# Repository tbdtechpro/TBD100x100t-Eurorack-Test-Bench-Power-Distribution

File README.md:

# TBD100x100t Eurorack Test Bench Power Distribution
 Eurorack distribution board with banana jack sockets for inputs and test probe sockets and a terminal block at the end of the circuit.

 This is part of a series of 100mm x 100mm Power Distribution boards I'm putting together. There is also a default board and an extension board.
 The size was chosen to allow for cheap manufacture with the prototype PCB providers.

 TBD-100x100t is intended for test bench usage: checking DIY modules and power supplies before they go anywhere near a rack. I run mine from a Mean Well triple output supply (+12v, -12v and 5v) in an enclosure with banana jacks.

## Rev 0.2 - now in KiCad
 The board was originally drawn in DipTrace back in 2020. It has now been migrated to KiCad 9 and reworked to fix some issues with that original draft.
 I have not had rev 0.2 manufactured yet, so it is untested at this time. It passes KiCad's ERC and DRC checks.

 What changed from the original draft:
 - The 5v rail is finished. On the original the 5v bus was never joined to its filter, two of its capacitors were not grounded and 5v never reached the terminal block.
 - Four 16 pin headers instead of six. The original headers were too close together to use without skipping every other one, at least with the cables I had. They are now 22mm apart.
 - The banana jacks are on the standard 19.05mm spacing with 1.6mm holes. The original spacing and holes were too small for the Cal Test jacks in the BOM.
 - Each rail is still a Pi filter but with a 10uH inductor in place of the ferrite bead (which is now obsolete), and most of the capacitance moved to the bus side: 47uF, 10uH, then 1000uF with 10uF and 100nF ceramics.
 - Each rail has a resettable fuse, a Schottky diode to ground so a swapped lead trips the fuse, and an LED after the fuse.
 - Each rail has a two pin link. Pull the jumper and put a multimeter across the pins to read how much current a module draws.
 - Loop test points at each input show what the supply is delivering. The four test probe sockets are on the bus and show what the modules see. They now sit at the top edge of the board so a multimeter probe can reach them. There are two ground loops for an oscilloscope clip.

 The headers have pin 1 (-12v, the red stripe) at the bottom, same as the original.

## Files
 - `kicad/` is the KiCad 9 project: schematic and board.
 - `TBD100x100t_rev0.2_schematic.pdf` is the schematic.
 - `TBD100x100t_rev0.2_gerbers.zip` has the gerbers and drill files.
 - `TBD 100x100t  BOM.csv` has the parts and values with manufacturer part numbers.
 - `3drender.png` and `3drender-top.png` are renders of the board.
 - `original-diptrace/` keeps the 2020 DipTrace files, gerbers, BOM and render, plus `kicad-port/`, a KiCad copy of that original board exactly as it was drawn, faults included.

 The banana jack, test probe socket, fuse, terminal block and inductor footprints come from my [tbd-kicad](https://github.com/tbdtechpro/tbd-kicad) library. The board file carries its own copies so it opens without the library, but you will want it if you plan to edit those parts.

## Things to check before ordering
 - The test probe socket footprint follows the pattern from the 2020 board. Cinch only supplies the drawing on request, so I have not been able to verify it.
 - The header spacing is close to, but not exactly, the spacing I know works with my cables.
 - The -12v fuse is 1.1A like the other two, which is more than the 0.5A a Mean Well RT-65B is rated for on that rail.

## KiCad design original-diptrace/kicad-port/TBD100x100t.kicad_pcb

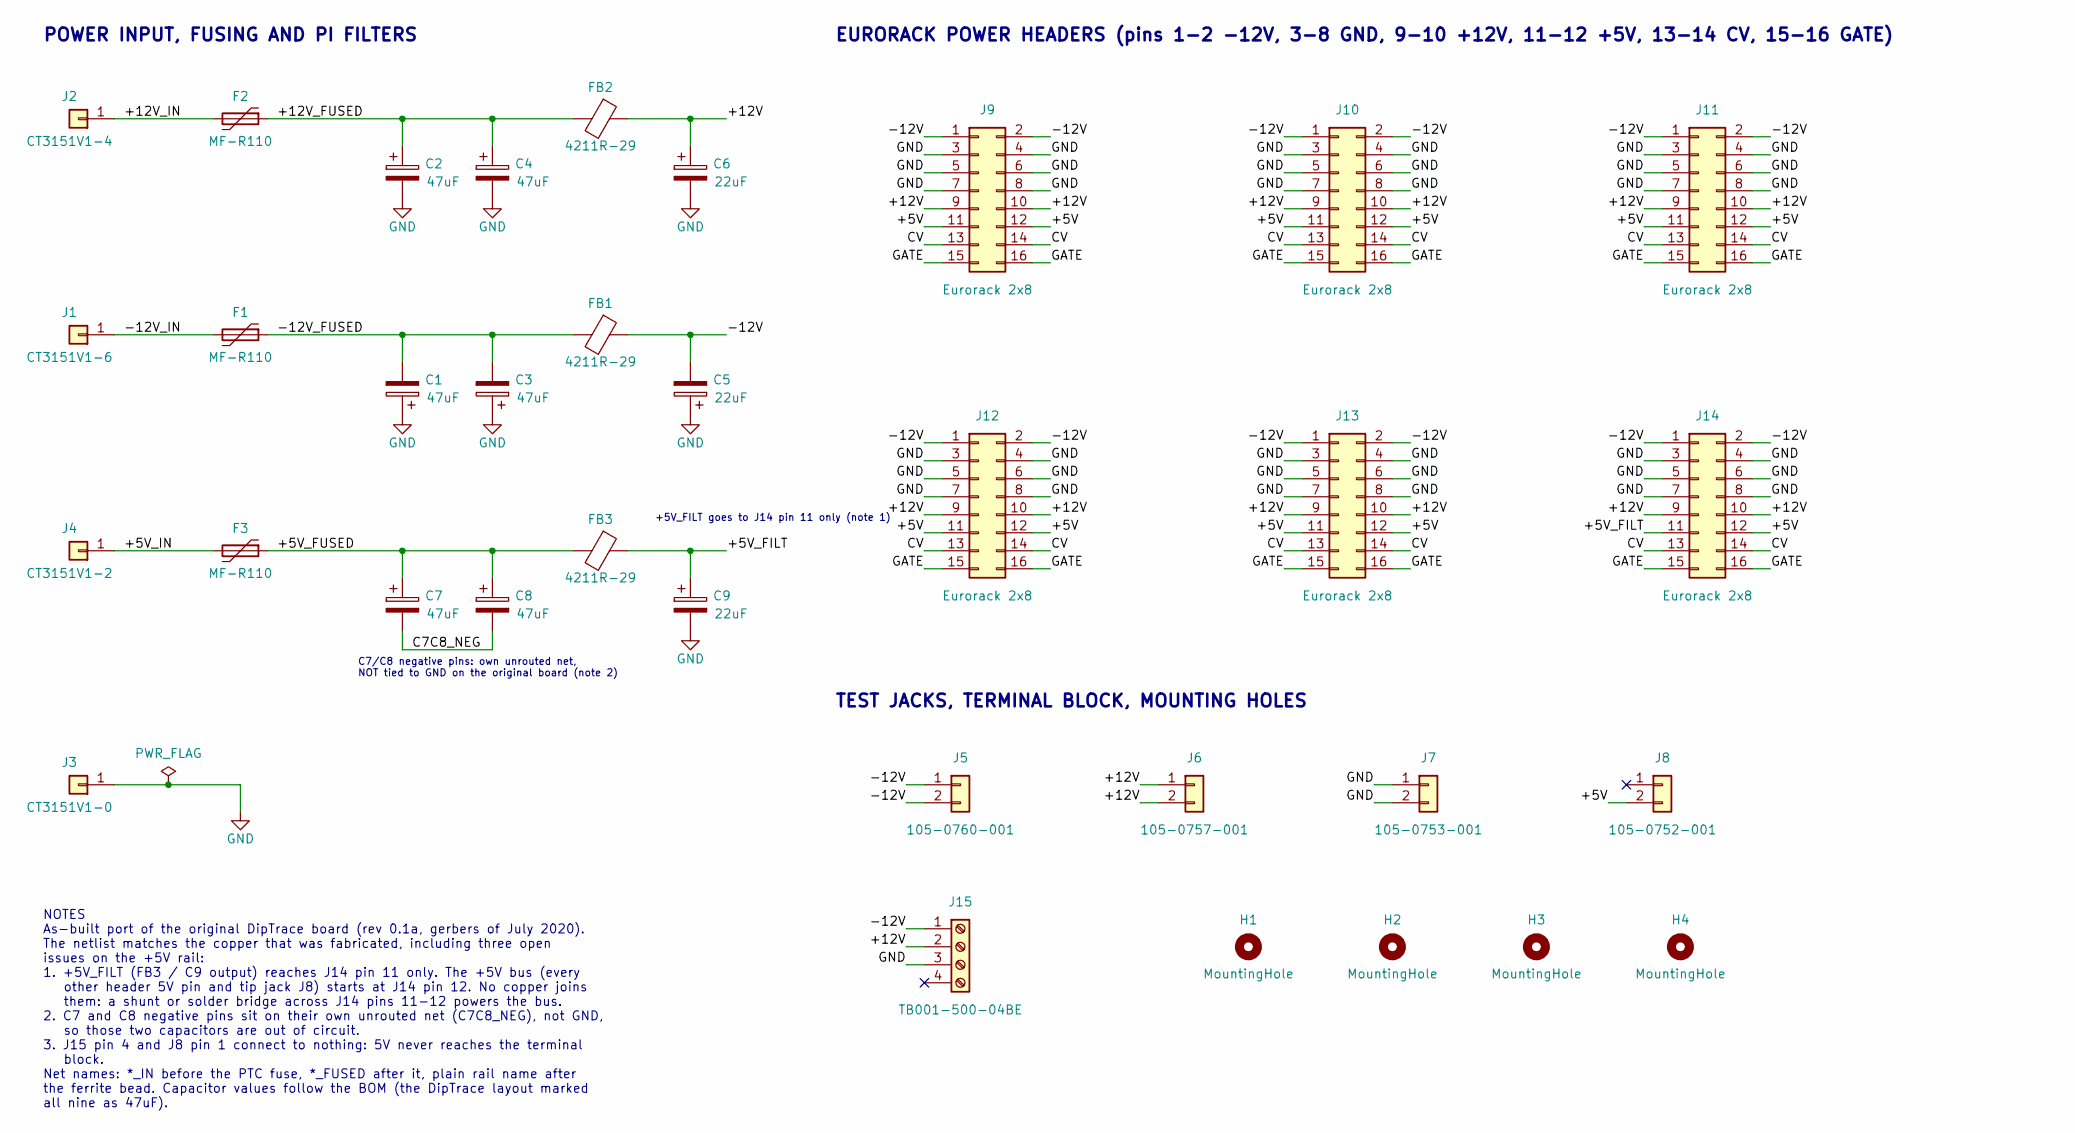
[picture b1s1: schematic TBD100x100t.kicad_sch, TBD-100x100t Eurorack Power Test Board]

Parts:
C1, C2, C3, C4, C7, C8: 47uF; CP_Radial_D4.4mm_P5.08mm; Mouser 667-EEU-FC1J470B
C5, C6, C9: 22uF; CP_Radial_D4.4mm_P5.08mm; Mouser 667-EEU-FC1H220B
F1, F2, F3: MF-R110; Fuse_PTC_Bourns_MF-R110_P5.1mm; Mouser 652-MF-R110-2
FB1, FB2, FB3: 4211R-29; FerriteBead_Axial_L13.8mm_D3.5mm_P27.8mm; Mouser 807-4211R-29TR
H1, H2, H3, H4: MountingHole; MountingHole_3.0mm_NPTH
J1: CT3151V1-6; BananaJack_CalTest_CT3151V1_Vertical; Mouser 510-CT3151V1-6
J2: CT3151V1-4; BananaJack_CalTest_CT3151V1_Vertical; Mouser 510-CT3151V1-4
J3: CT3151V1-0; BananaJack_CalTest_CT3151V1_Vertical; Mouser 510-CT3151V1-0
J4: CT3151V1-2; BananaJack_CalTest_CT3151V1_Vertical; Mouser 510-CT3151V1-2
J5: 105-0760-001; TipJack_Johnson_105-07xx_Horizontal; Mouser 530-105-0760-1
J6: 105-0757-001; TipJack_Johnson_105-07xx_Horizontal; Mouser 530-105-0757-1
J7: 105-0753-001; TipJack_Johnson_105-07xx_Horizontal; Mouser 530-105-0753-150
J8: 105-0752-001; TipJack_Johnson_105-07xx_Horizontal; Mouser 530-105-0752-1
J9, J10, J11, J12, J13, J14: Eurorack 2x8; PinHeader_2x08_P2.54mm_Eurorack; Mouser 517-N2516-6002RB
J15: TB001-500-04BE; TerminalBlock_CUI_TB001-500-04BE_1x04_P5.00mm; Mouser 490-TB001-500-04BE

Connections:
/+5V: J8.2, J9.11, J9.12, J10.11, J10.12, J11.11, J11.12, J12.11, J12.12, J13.11, J13.12, J14.12
/+5V_FILT: C9.1, FB3.1, J14.11
/+5V_FUSED: C7.1, C8.1, F3.1, FB3.2
/+5V_IN: F3.2, J4.1
/+12V: C6.1, FB2.1, J6.1, J6.2, J9.9, J9.10, J10.9, J10.10, J11.9, J11.10, J12.9, J12.10, J13.9, J13.10, J14.9, J14.10, J15.2
/+12V_FUSED: C2.1, C4.1, F2.1, FB2.2
/+12V_IN: F2.2, J2.1
/-12V: C5.2, FB1.1, J5.1, J5.2, J9.1, J9.2, J10.1, J10.2, J11.1, J11.2, J12.1, J12.2, J13.1, J13.2, J14.1, J14.2, J15.1
/-12V_FUSED: C1.2, C3.2, F1.1, FB1.2
/-12V_IN: F1.2, J1.1
/C7C8_NEG: C7.2, C8.2
/CV: J9.13, J9.14, J10.13, J10.14, J11.13, J11.14, J12.13, J12.14, J13.13, J13.14, J14.13, J14.14
/GATE: J9.15, J9.16, J10.15, J10.16, J11.15, J11.16, J12.15, J12.16, J13.15, J13.16, J14.15, J14.16
GND: C1.1, C2.2, C3.1, C4.2, C5.1, C6.2, C9.2, J3.1, J7.1, J7.2, J9.3, J9.4, J9.5, J9.6, J9.7, J9.8, J10.3, J10.4, J10.5, J10.6, J10.7, J10.8, J11.3, J11.4, J11.5, J11.6, J11.7, J11.8, J12.3, J12.4, J12.5, J12.6, J12.7, J12.8, J13.3, J13.4, J13.5, J13.6, J13.7, J13.8, J14.3, J14.4, J14.5, J14.6, J14.7, J14.8, J15.3

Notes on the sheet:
POWER INPUT, FUSING AND PI FILTERS
C7/C8 negative pins: own unrouted net, NOT tied to GND on the original board (note 2)
+5V_FILT goes to J14 pin 11 only (note 1)
EURORACK POWER HEADERS (pins 1-2 -12V, 3-8 GND, 9-10 +12V, 11-12 +5V, 13-14 CV, 15-16 GATE)
TEST JACKS, TERMINAL BLOCK, MOUNTING HOLES
NOTES As-built port of the original DipTrace board (rev 0.1a, gerbers of July 2020). The netlist matches the copper that was fabricated, including three open issues on the +5V rail: 1. +5V_FILT (FB3 / C9 output) reaches J14 pin 11 only. The +5V bus (every other header 5V pin and tip jack J8) starts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

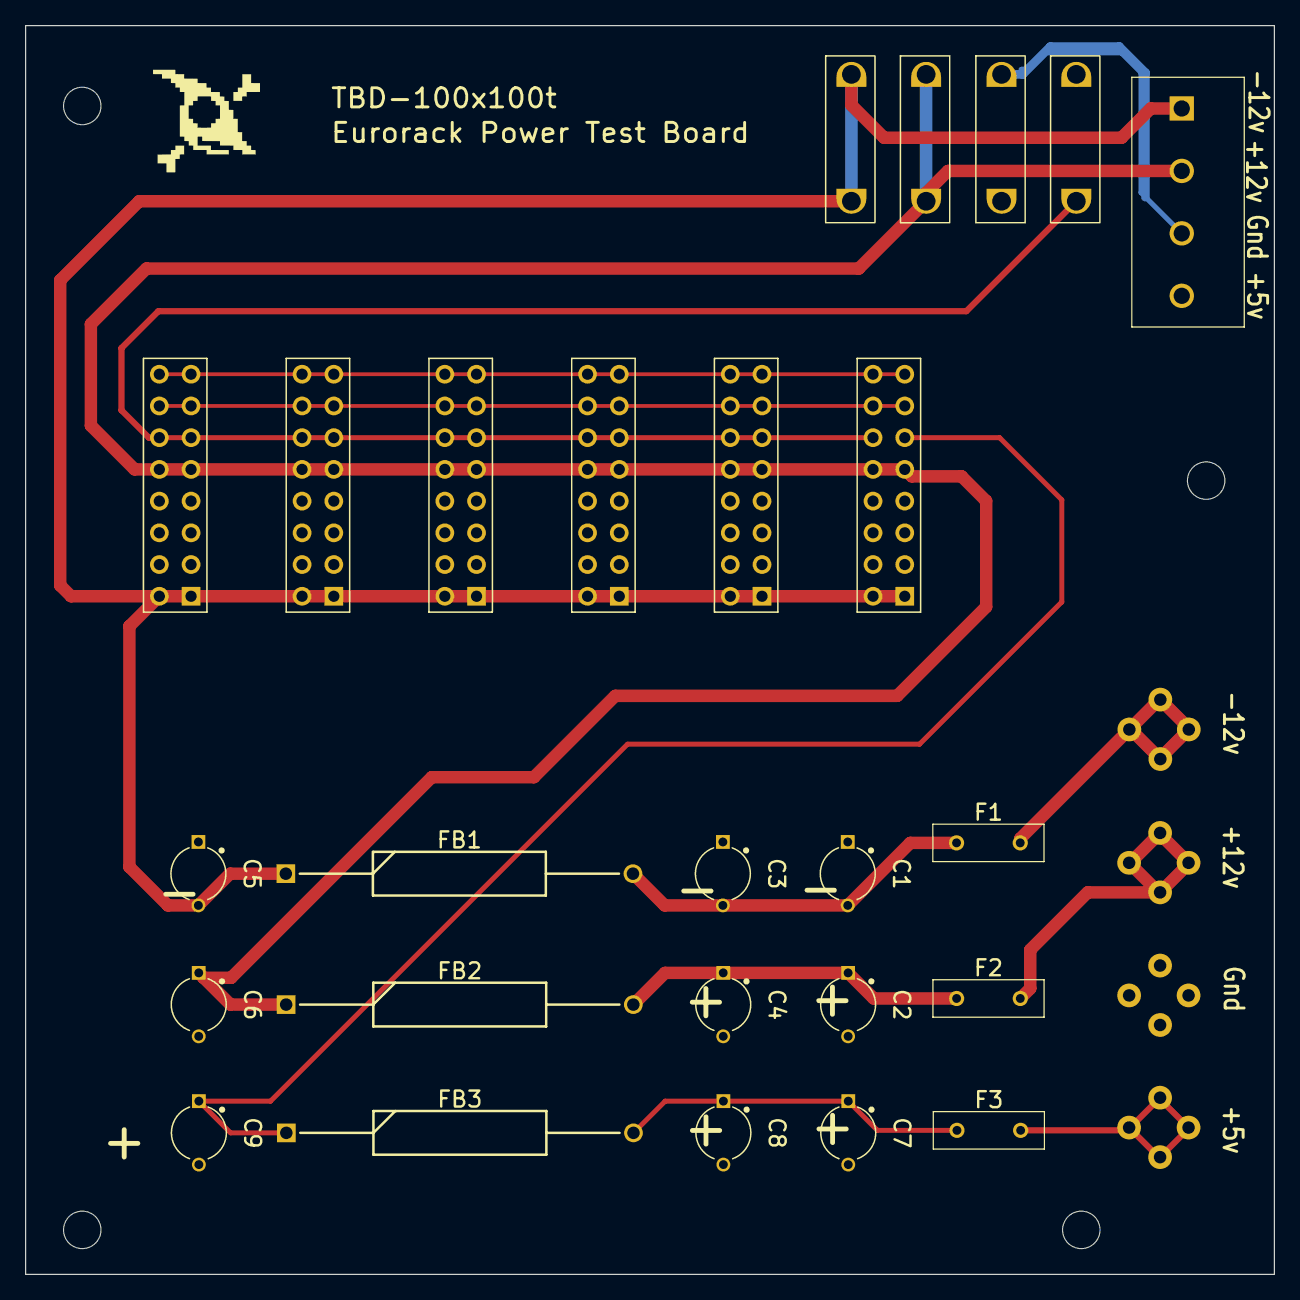
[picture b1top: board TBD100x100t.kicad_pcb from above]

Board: 2 copper layers, 100.0 x 100.0 mm, 34 parts (0 on the bottom side), 14 nets.

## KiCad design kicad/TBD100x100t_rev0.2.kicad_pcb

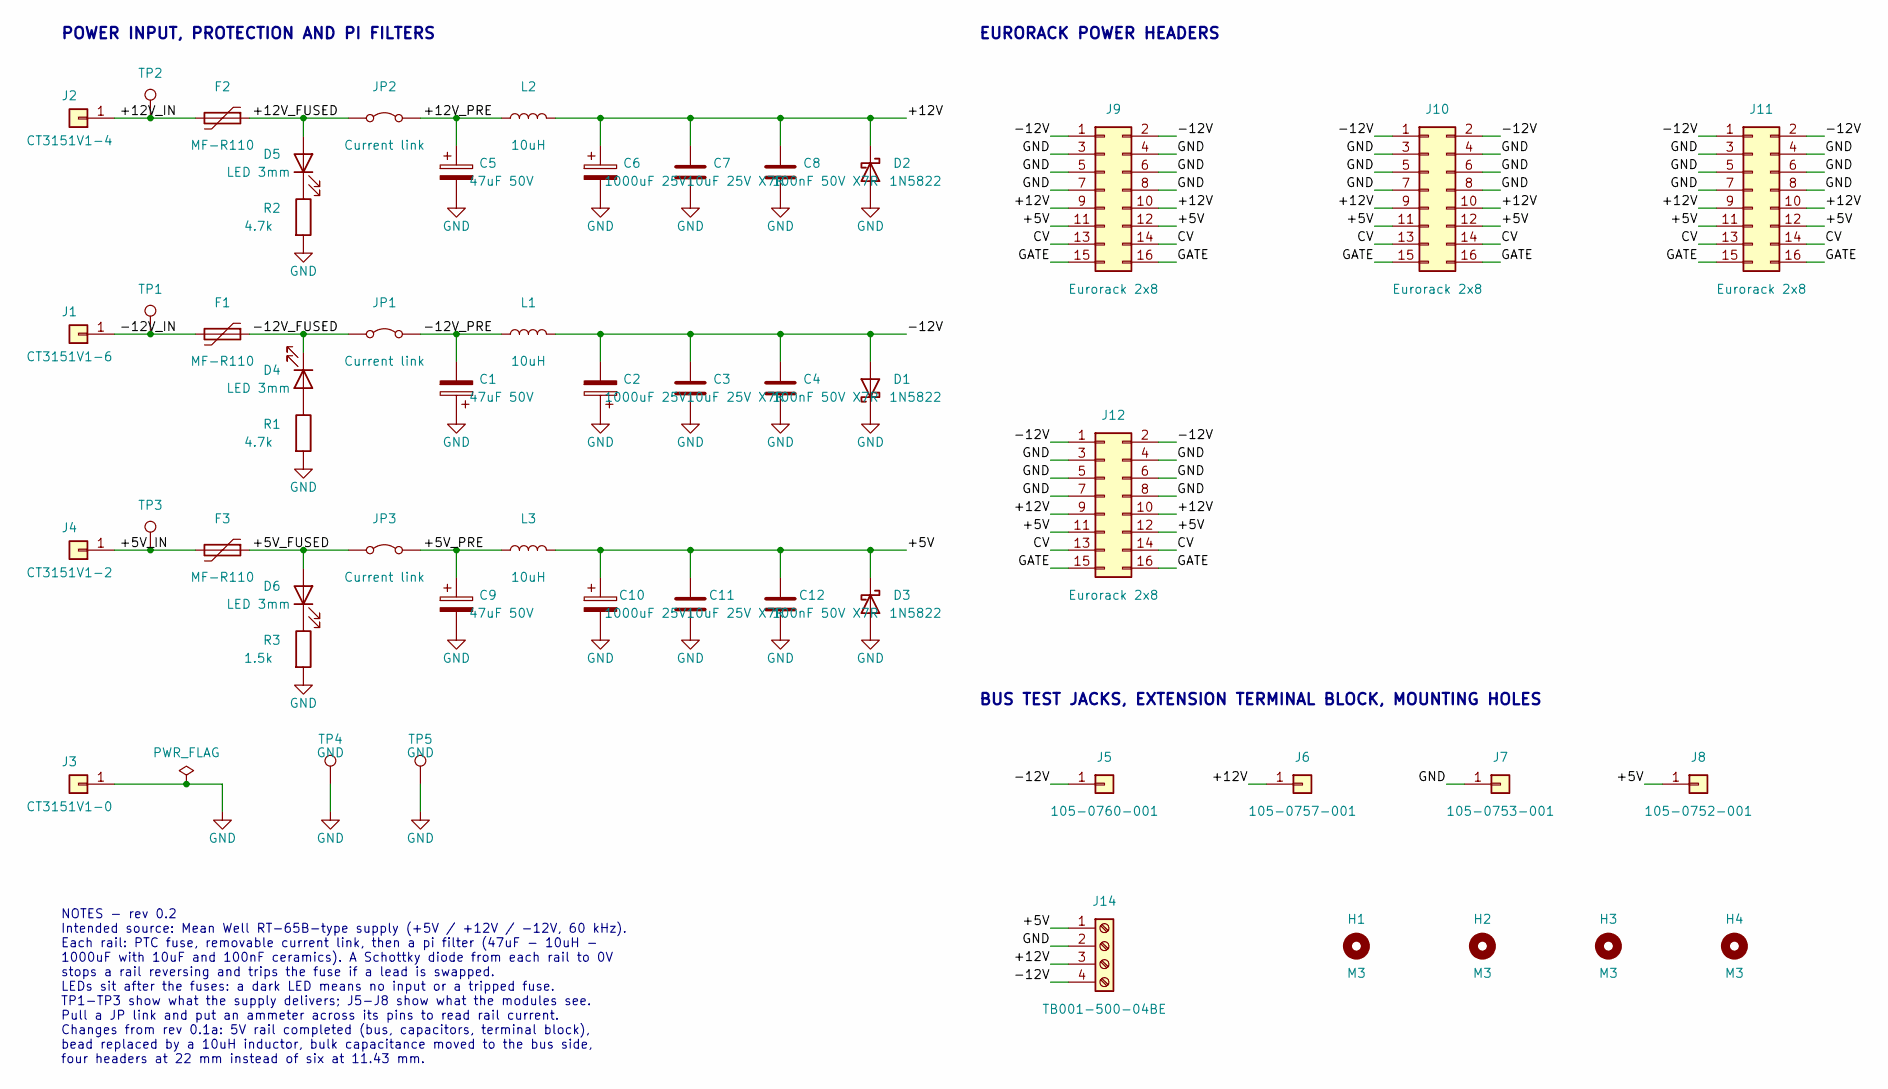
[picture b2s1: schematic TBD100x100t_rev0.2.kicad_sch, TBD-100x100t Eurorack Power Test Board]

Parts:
C1, C5, C9: 47uF 50V; CP_Radial_D6.3mm_P2.50mm; MPN EEU-FR1H470
C2, C6, C10: 1000uF 25V; CP_Radial_D10.0mm_P5.00mm; MPN EEU-FR1E102
C3, C7, C11: 10uF 25V X7R; C_Disc_D6.0mm_W4.4mm_P5.00mm; MPN FG26X7R1E106KRT06
C4, C8, C12: 100nF 50V X7R; C_Disc_D5.0mm_W2.5mm_P5.00mm; MPN FG28X7R1H104KNT06
D1, D2, D3: 1N5822; D_DO-201AD_P12.70mm_Horizontal; MPN 1N5822
D4, D5, D6: LED 3mm; LED_D3.0mm
F1, F2, F3: MF-R110; Fuse_Bourns_MF-R110; MPN MF-R110
H1, H2, H3, H4: M3; MountingHole_3.2mm_M3
J1: CT3151V1-6; Banana_CalTest_CT3151V1_Vertical; MPN CT3151V1-6
J2: CT3151V1-4; Banana_CalTest_CT3151V1_Vertical; MPN CT3151V1-4
J3: CT3151V1-0; Banana_CalTest_CT3151V1_Vertical; MPN CT3151V1-0
J4: CT3151V1-2; Banana_CalTest_CT3151V1_Vertical; MPN CT3151V1-2
J5: 105-0760-001; TipJack_Johnson_105-075x_Horizontal_P10.16mm; MPN 105-0760-001
J6: 105-0757-001; TipJack_Johnson_105-075x_Horizontal_P10.16mm; MPN 105-0757-001
J7: 105-0753-001; TipJack_Johnson_105-075x_Horizontal_P10.16mm; MPN 105-0753-001
J8: 105-0752-001; TipJack_Johnson_105-075x_Horizontal_P10.16mm; MPN 105-0752-001
J9, J10, J11, J12: Eurorack 2x8; IDC-Header_2x08_P2.54mm_Vertical; MPN N2516-6002RB
J14: TB001-500-04BE; TerminalBlock_SameSky_TB001-500-04_1x04_P5.00mm; MPN TB001-500-04BE
JP1, JP2, JP3: Current link; PinHeader_1x02_P2.54mm_Vertical
L1, L2, L3: 10uH; L_Radial_D8.7mm_H12.0mm_P5.00mm_Bourns_RLB0914; MPN RLB0914-100KL
R1, R2: 4.7k; R_Axial_DIN0207_L6.3mm_D2.5mm_P7.62mm_Horizontal
R3: 1.5k; R_Axial_DIN0207_L6.3mm_D2.5mm_P7.62mm_Horizontal
TP1: -12V IN; TestPoint_Keystone_5010-5014_Multipurpose; MPN 5010
TP2: +12V IN; TestPoint_Keystone_5010-5014_Multipurpose; MPN 5010
TP3: +5V IN; TestPoint_Keystone_5010-5014_Multipurpose; MPN 5010
TP4, TP5: GND; TestPoint_Keystone_5010-5014_Multipurpose; MPN 5011

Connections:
/+5V: C10.1, C11.1, C12.1, D3.1 (K), J8.1, J9.11, J9.12, J10.11, J10.12, J11.11, J11.12, J12.11, J12.12, J14.1, L3.2
/+5V_FUSED: D6.2 (A), F3.1, JP3.1 (A)
/+5V_IN: F3.2, J4.1, TP3.1
/+5V_PRE: C9.1, JP3.2 (B), L3.1
/+12V: C6.1, C7.1, C8.1, D2.1 (K), J6.1, J9.9, J9.10, J10.9, J10.10, J11.9, J11.10, J12.9, J12.10, J14.3, L2.2
/+12V_FUSED: D5.2 (A), F2.1, JP2.1 (A)
/+12V_IN: F2.2, J2.1, TP2.1
/+12V_PRE: C5.1, JP2.2 (B), L2.1
/-12V: C2.2, C3.1, C4.1, D1.2 (A), J5.1, J9.1, J9.2, J10.1, J10.2, J11.1, J11.2, J12.1, J12.2, J14.4, L1.2
/-12V_FUSED: D4.1 (K), F1.1, JP1.1 (A)
/-12V_IN: F1.2, J1.1, TP1.1
/-12V_PRE: C1.2, JP1.2 (B), L1.1
/CV: J9.13, J9.14, J10.13, J10.14, J11.13, J11.14, J12.13, J12.14
/GATE: J9.15, J9.16, J10.15, J10.16, J11.15, J11.16, J12.15, J12.16
GND: C1.1, C2.1, C3.2, C4.2, C5.2, C6.2, C7.2, C8.2, C9.2, C10.2, C11.2, C12.2, D1.1 (K), D2.2 (A), D3.2 (A), J3.1, J7.1, J9.3, J9.4, J9.5, J9.6, J9.7, J9.8, J10.3, J10.4, J10.5, J10.6, J10.7, J10.8, J11.3, J11.4, J11.5, J11.6, J11.7, J11.8, J12.3, J12.4, J12.5, J12.6, J12.7, J12.8, J14.2, R1.2, R2.2, R3.2, TP4.1, TP5.1
unnamed: D4.2 (A), R1.1
unnamed: D5.1 (K), R2.1
unnamed: D6.1 (K), R3.1

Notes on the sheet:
POWER INPUT, PROTECTION AND PI FILTERS
EURORACK POWER HEADERS
BUS TEST JACKS, EXTENSION TERMINAL BLOCK, MOUNTING HOLES
NOTES - rev 0.2 Intended source: Mean Well RT-65B-type supply (+5V / +12V / -12V, 60 kHz). Each rail: PTC fuse, removable current link, then a pi filter (47uF - 10uH - 1000uF with 10uF and 100nF ceramics). A Schottky diode from each rail to 0V stops a rail reversing and trips the fuse if a lead is 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

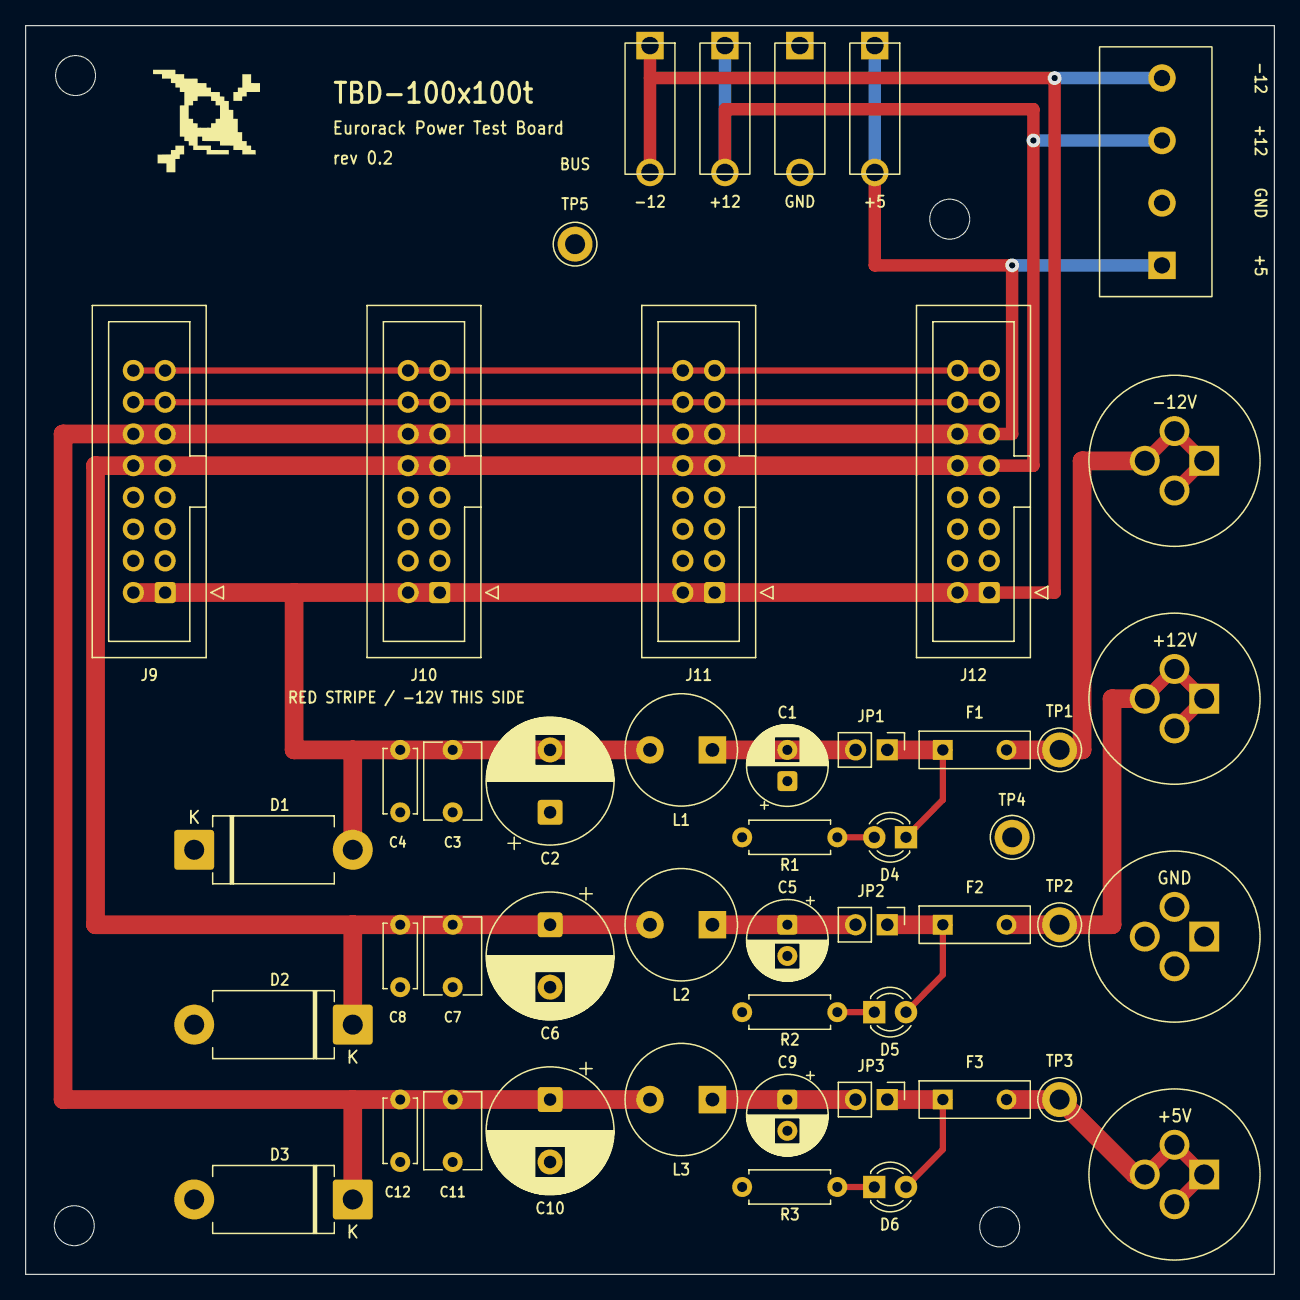
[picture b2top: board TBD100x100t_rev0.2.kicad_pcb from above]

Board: 2 copper layers, 100.0 x 100.0 mm, 52 parts (0 on the bottom side), 18 nets.

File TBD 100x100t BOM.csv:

Refs,Qty,Value,Manufacturer,Part number,Footprint,Description
"C1, C5, C9",3,47uF 50V,Panasonic,EEU-FR1H470,CP_Radial_D6.3mm_P2.50mm,"Low-ESR electrolytic, filter input leg"
"C2, C6, C10",3,1000uF 25V,Panasonic,EEU-FR1E102,CP_Radial_D10.0mm_P5.00mm,"Low-ESR electrolytic, filter output leg / bus reservoir"
"C3, C7, C11",3,10uF 25V X7R,TDK,FG26X7R1E106KRT06,C_Disc_D6.0mm_W4.4mm_P5.00mm,"Radial MLCC, high-frequency bypass on the bus"
"C4, C8, C12",3,100nF 50V X7R,TDK,FG28X7R1H104KNT06,C_Disc_D5.0mm_W2.5mm_P5.00mm,"Radial MLCC, high-frequency bypass on the bus"
"D1, D2, D3",3,1N5822,onsemi / Vishay,1N5822,D_DO-201AD_P12.70mm_Horizontal,"Schottky clamp to 0V: stops the rail reversing, trips the fuse on a swapped lead"
D4,1,LED 3mm,,,LED_D3.0mm,"Rail-alive indicator, -12V after the fuse"
D5,1,LED 3mm,,,LED_D3.0mm,"Rail-alive indicator, +12V after the fuse"
D6,1,LED 3mm,,,LED_D3.0mm,"Rail-alive indicator, +5V after the fuse"
"F1, F2, F3",3,MF-R110,Bourns,MF-R110,Fuse_Bourns_MF-R110,"PPTC resettable fuse, 1.1 A hold, 2.2 A trip, 30 V"
J1,1,CT3151V1-6,Cal Test Electronics,CT3151V1-6,Banana_CalTest_CT3151V1_Vertical,"Banana jack, -12V in"
J2,1,CT3151V1-4,Cal Test Electronics,CT3151V1-4,Banana_CalTest_CT3151V1_Vertical,"Banana jack, +12V in"
J3,1,CT3151V1-0,Cal Test Electronics,CT3151V1-0,Banana_CalTest_CT3151V1_Vertical,"Banana jack, 0V"
J4,1,CT3151V1-2,Cal Test Electronics,CT3151V1-2,Banana_CalTest_CT3151V1_Vertical,"Banana jack, +5V in"
J5,1,105-0760-001,Cinch / Johnson,105-0760-001,TipJack_Johnson_105-075x_Horizontal_P10.16mm,"Tip jack on the bus, -12V (what the modules see)"
J6,1,105-0757-001,Cinch / Johnson,105-0757-001,TipJack_Johnson_105-075x_Horizontal_P10.16mm,"Tip jack on the bus, +12V (what the modules see)"
J7,1,105-0753-001,Cinch / Johnson,105-0753-001,TipJack_Johnson_105-075x_Horizontal_P10.16mm,"Tip jack on the bus, GND (what the modules see)"
J8,1,105-0752-001,Cinch / Johnson,105-0752-001,TipJack_Johnson_105-075x_Horizontal_P10.16mm,"Tip jack on the bus, +5V (what the modules see)"
"J9, J10, J11, J12",4,Eurorack 2x8,3M,N2516-6002RB,IDC-Header_2x08_P2.54mm_Vertical,"Eurorack 16-pin shrouded power header, pin 1 (-12V) at the bottom"
J14,1,TB001-500-04BE,Same Sky (CUI Devices),TB001-500-04BE,TerminalBlock_SameSky_TB001-500-04_1x04_P5.00mm,"Terminal block to an extension board; top to bottom -12V, +12V, 0V, +5V (pin 1 is +5V)"
JP1,1,Current link,,,PinHeader_1x02_P2.54mm_Vertical,2-pin header with shunt: remove to put an ammeter in series with -12V
JP2,1,Current link,,,PinHeader_1x02_P2.54mm_Vertical,2-pin header with shunt: remove to put an ammeter in series with +12V
JP3,1,Current link,,,PinHeader_1x02_P2.54mm_Vertical,2-pin header with shunt: remove to put an ammeter in series with +5V
"L1, L2, L3",3,10uH,Bourns,RLB0914-100KL,L_Radial_D8.7mm_H12.0mm_P5.00mm_Bourns_RLB0914,"Radial power inductor, 2.7 A, 48 mOhm max; filter series element (replaces obsolete 4211R-29 bead)"
"R1, R2",2,4.7k,,,R_Axial_DIN0207_L6.3mm_D2.5mm_P7.62mm_Horizontal,"LED series resistor, 0.25 W"
R3,1,1.5k,,,R_Axial_DIN0207_L6.3mm_D2.5mm_P7.62mm_Horizontal,"LED series resistor, 0.25 W"
TP1,1,-12V IN,Keystone,5010,TestPoint_Keystone_5010-5014_Multipurpose,"Test loop, -12V at the input (what the supply delivers)"
TP2,1,+12V IN,Keystone,5010,TestPoint_Keystone_5010-5014_Multipurpose,"Test loop, +12V at the input (what the supply delivers)"
TP3,1,+5V IN,Keystone,5010,TestPoint_Keystone_5010-5014_Multipurpose,"Test loop, +5V at the input (what the supply delivers)"
TP4,1,GND,Keystone,5011,TestPoint_Keystone_5010-5014_Multipurpose,"Ground loop for a scope clip, input side"
TP5,1,GND,Keystone,5011,TestPoint_Keystone_5010-5014_Multipurpose,"Ground loop for a scope clip, bus side"
